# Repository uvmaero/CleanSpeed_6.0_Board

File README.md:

# AERO_2023_2024_Board* singular

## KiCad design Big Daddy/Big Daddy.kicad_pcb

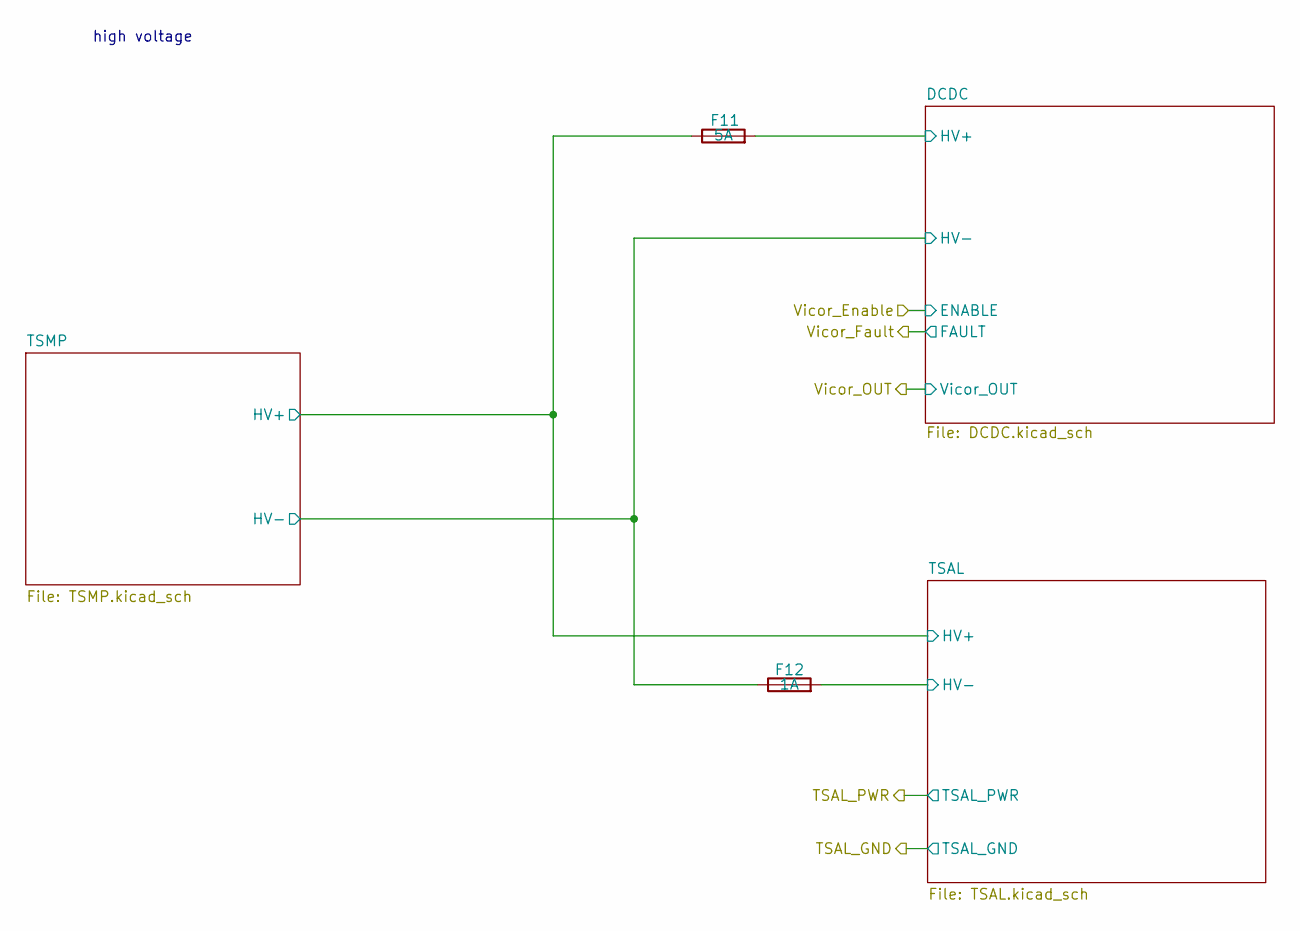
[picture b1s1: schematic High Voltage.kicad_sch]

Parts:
F11: 5A; Fuseholder_Cylinder-5x20mm_Schurter_0031_8201_Horizontal_Op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
F12: 1A; Fuseholder_Cylinder-5x20mm_Schurter_0031_8201_Horizontal_Op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

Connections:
/High Voltage/DCDC/HV+: F11.2; also elsewhere on the board
/High Voltage/DCDC/HV-: F12.1; also elsewhere on the board
/High Voltage/TSAL/HV+: F11.1; also elsewhere on the board
/High Voltage/TSAL/HV-: F12.2; also elsewhere on the board

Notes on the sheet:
high voltage

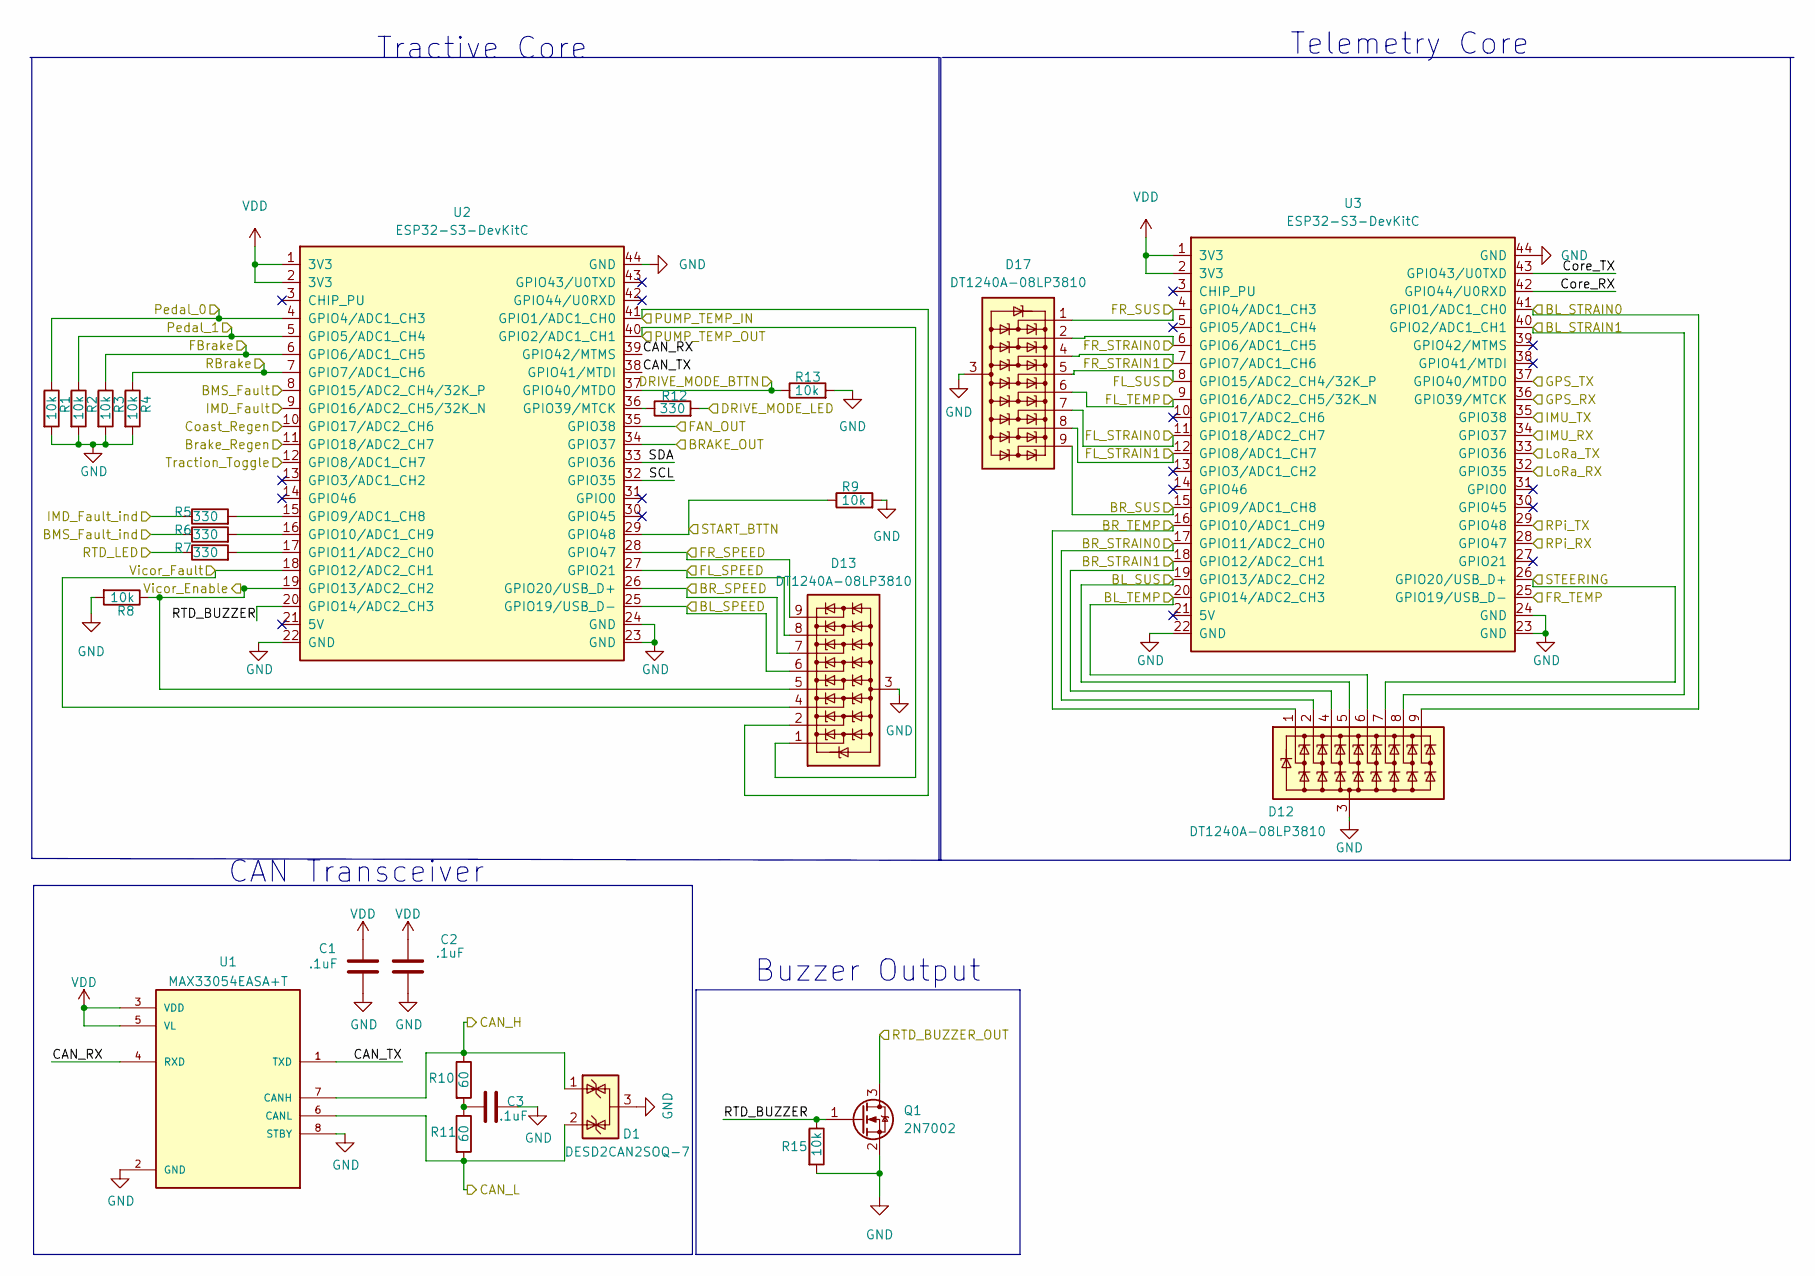
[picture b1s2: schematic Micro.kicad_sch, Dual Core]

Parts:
C1, C2, C3: .1uF; C_0603_1608Metric_Pad1.08x0.95mm_HandSolder; Manufacturer_Part_Number CC0603KRX7R7BB104; Digikey part number 311-1088-1-ND
D1: DESD2CAN2SOQ-7; SOT-23; Manufacturer_Part_Number DESD2CAN2SOQ-7; Digikey part number DESD2CAN2SOQ-7DICT-ND
D12, D13, D17: DT1240A-08LP3810; UDFN-9_1.0x3.8mm_P0.5mm; Manufacturer_Part_Number DT1240A-08LP3810-7; Digikey part number DT1240A-08LP3810-7DICT-ND
Q1: 2N7002; SOT-23; Manufacturer_Part_Number 2N7002; Digikey part number 2N7002NCT-ND
R1, R2, R3, R4, R8, R9, R13, R15: 10k; R_0603_1608Metric_Pad0.98x0.95mm_HandSolder; Manufacturer_Part_Number RK73H1JTTD1002F; Digikey part number 2019-RK73H1JTTD1002FCT-ND
R5, R6, R7, R12: 330; R_0603_1608Metric_Pad0.98x0.95mm_HandSolder; Manufacturer_Part_Number WK73R1JTTD331J; Digikey part number 2019-WK73R1JTTD331JCT-ND
R10, R11: 60; R_0603_1608Metric_Pad0.98x0.95mm_HandSolder; Manufacturer_Part_Number P0603C60R0BNT; Digikey part number 716-P0603C60R0BNTCT-ND
U1: MAX33054EASA+T; SOIC127P600X175-8N; Manufacturer_Part_Number MAX33054EASA+T; Digikey part number 175-MAX33054EASA+TCT-ND
U2, U3: ESP32-S3-DevKitC; Manufacturer_Part_Number ESP32-S3-DEVKITC-1U-N8R8; Digikey part number 1965-ESP32-S3-DEVKITC-1U-N8R8-ND

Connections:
/Connectors/BL_SPEED: D13.6 (K5), U2.25 (GPIO19/USB_D-); also elsewhere on the board
/Connectors/BL_STRAIN0: D12.9 (K8), U3.41 (GPIO1/ADC1_CH0); also elsewhere on the board
/Connectors/BL_STRAIN1: D12.8 (K7), U3.40 (GPIO2/ADC1_CH1); also elsewhere on the board
/Connectors/BL_SUS: D12.5 (K4), U3.19 (GPIO13/ADC2_CH2); also elsewhere on the board
/Connectors/BL_TEMP: D12.6 (K5), U3.20 (GPIO14/ADC2_CH3); also elsewhere on the board
/Connectors/BMS_Fault_ind: R6.1; also elsewhere on the board
/Connectors/BR_SPEED: D13.7 (K6), U2.26 (GPIO20/USB_D+); also elsewhere on the board
/Connectors/BR_STRAIN0: D12.2 (K2), U3.17 (GPIO11/ADC2_CH0); also elsewhere on the board
/Connectors/BR_STRAIN1: D12.4 (K3), U3.18 (GPIO12/ADC2_CH1); also elsewhere on the board
/Connectors/BR_SUS: D17.9 (K8), U3.15 (GPIO9/ADC1_CH8); also elsewhere on the board
/Connectors/BR_TEMP: D12.1 (K1), U3.16 (GPIO10/ADC1_CH9); also elsewhere on the board
/Connectors/Brake_Regen: U2.11 (GPIO18/ADC2_CH7); also elsewhere on the board
/Connectors/CAN_H: D1.1 (K), R10.1, U1.7 (CANH); also elsewhere on the board
/Connectors/CAN_L: D1.2 (K), R11.2, U1.6 (CANL); also elsewhere on the board
/Connectors/Coast_Regen: U2.10 (GPIO17/ADC2_CH6); also elsewhere on the board
/Connectors/DRIVE_MODE_BTTN: R13.1, U2.37 (GPIO40/MTDO); also elsewhere on the board
/Connectors/DRIVE_MODE_LED: R12.2; also elsewhere on the board
/Connectors/FBrake: R3.1, U2.6 (GPIO6/ADC1_CH5); also elsewhere on the board
/Connectors/FL_SPEED: D13.8 (K7), U2.27 (GPIO21); also elsewhere on the board
/Connectors/FL_STRAIN0: D17.7 (K6), U3.11 (GPIO18/ADC2_CH7); also elsewhere on the board
/Connectors/FL_STRAIN1: D17.8 (K7), U3.12 (GPIO8/ADC1_CH7); also elsewhere on the board
/Connectors/FL_SUS: D17.5 (K4), U3.8 (GPIO15/ADC2_CH4/32K_P); also elsewhere on the board
/Connectors/FL_TEMP: D17.6 (K5), U3.9 (GPIO16/ADC2_CH5/32K_N); also elsewhere on the board
/Connectors/FR_SPEED: D13.9 (K8), U2.28 (GPIO47); also elsewhere on the board
/Connectors/FR_STRAIN0: D17.2 (K2), U3.6 (GPIO6/ADC1_CH5); also elsewhere on the board
/Connectors/FR_STRAIN1: D17.4 (K3), U3.7 (GPIO7/ADC1_CH6); also elsewhere on the board
/Connectors/FR_SUS: D17.1 (K1), U3.4 (GPIO4/ADC1_CH3); also elsewhere on the board
/Connectors/FR_TEMP: U3.25 (GPIO19/USB_D-); also elsewhere on the board
/Connectors/GPS_RX: U3.36 (GPIO39/MTCK); also elsewhere on the board
/Connectors/GPS_TX: U3.37 (GPIO40/MTDO); also elsewhere on the board
/Connectors/IMD_Fault_ind: R5.1; also elsewhere on the board
/Connectors/IMU_RX: U3.34 (GPIO37); also elsewhere on the board
/Connectors/IMU_TX: U3.35 (GPIO38); also elsewhere on the board
/Connectors/LoRa_RX: U3.32 (GPIO35); also elsewhere on the board
/Connectors/LoRa_TX: U3.33 (GPIO36); also elsewhere on the board
/Connectors/PUMP_TEMP_IN: D13.2 (K2), U2.41 (GPIO1/ADC1_CH0); also elsewhere on the board
/Connectors/PUMP_TEMP_OUT: D13.1 (K1), U2.40 (GPIO2/ADC1_CH1); also elsewhere on the board
/Connectors/Pedal_0: R1.1, U2.4 (GPIO4/ADC1_CH3); also elsewhere on the board
/Connectors/Pedal_1: R2.1, U2.5 (GPIO5/ADC1_CH4); also elsewhere on the board
/Connectors/RBrake: R4.1, U2.7 (GPIO7/ADC1_CH6); also elsewhere on the board
/Connectors/RPi_RX: U3.28 (GPIO47); also elsewhere on the board
/Connectors/RPi_TX: U3.29 (GPIO48); also elsewhere on the board
/Connectors/RTD_BUZZER_OUT: Q1.3 (D); also elsewhere on the board
/Connectors/RTD_LED: R7.1; also elsewhere on the board
/Connectors/START_BTTN: R9.1, U2.29 (GPIO48); also elsewhere on the board
/Connectors/STEERING: D12.7 (K6), U3.26 (GPIO20/USB_D+); also elsewhere on the board
/Cooling/Brake_SIG_Out: U2.34 (GPIO37); also elsewhere on the board
/Cooling/Fan_SIG_Out: U2.35 (GPIO38); also elsewhere on the board
/High Voltage/Vicor_Enable: D13.5 (K4), R8.1, U2.19 (GPIO13/ADC2_CH2); also elsewhere on the board
/High Voltage/Vicor_Fault: D13.4 (K3), U2.18 (GPIO12/ADC2_CH1); also elsewhere on the board
/Latching/BMS_IND: U2.8 (GPIO15/ADC2_CH4/32K_P); also elsewhere on the board
/Latching/IMD_IND: U2.9 (GPIO16/ADC2_CH5/32K_N); also elsewhere on the board
/Microcontrolller/CAN_RX: U1.4 (RXD), U2.39 (GPIO42/MTMS)
/Microcontrolller/CAN_TX: U1.1 (TXD), U2.38 (GPIO41/MTDI)
/Microcontrolller/Core_RX: U3.42 (GPIO44/U0RXD)
/Microcontrolller/Core_TX: U3.43 (GPIO43/U0TXD)
/Microcontrolller/RTD_BUZZER: Q1.1 (G), R15.1, U2.20 (GPIO14/ADC2_CH3)
/Microcontrolller/SCL: U2.32 (GPIO35)
/Microcontrolller/SDA: U2.33 (GPIO36)
/Microcontrolller/Traction_Toggle: U2.12 (GPIO8/ADC1_CH7)
GND: C1.2, C2.2, C3.2, D1.3 (A), D12.3 (A), D13.3 (A), D17.3 (A), Q1.2 (S), R1.2, R2.2, R3.2, R4.2, R8.2, R9.2, R13.2, R15.2, U1.2 (GND), U1.8 (STBY), U2.22 (GND), U2.23 (GND), U2.24 (GND), U2.44 (GND), U3.22 (GND), U3.23 (GND), U3.24 (GND), U3.44 (GND); also elsewhere on the board
unnamed: C3.1, R10.2, R11.1
unnamed: R5.2, U2.15 (GPIO9/ADC1_CH8)
unnamed: R6.2, U2.16 (GPIO10/ADC1_CH9)
unnamed: R7.2, U2.17 (GPIO11/ADC2_CH0)
unnamed: R12.1, U2.36 (GPIO39/MTCK)
VDD: C1.1, C2.1, U1.3 (VDD), U1.5 (VL), U2.1 (3V3), U2.2 (3V3), U3.1 (3V3), U3.2 (3V3); also elsewhere on the board

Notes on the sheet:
CAN Transceiver
Buzzer Output
Telemetry Core
Tractive Core

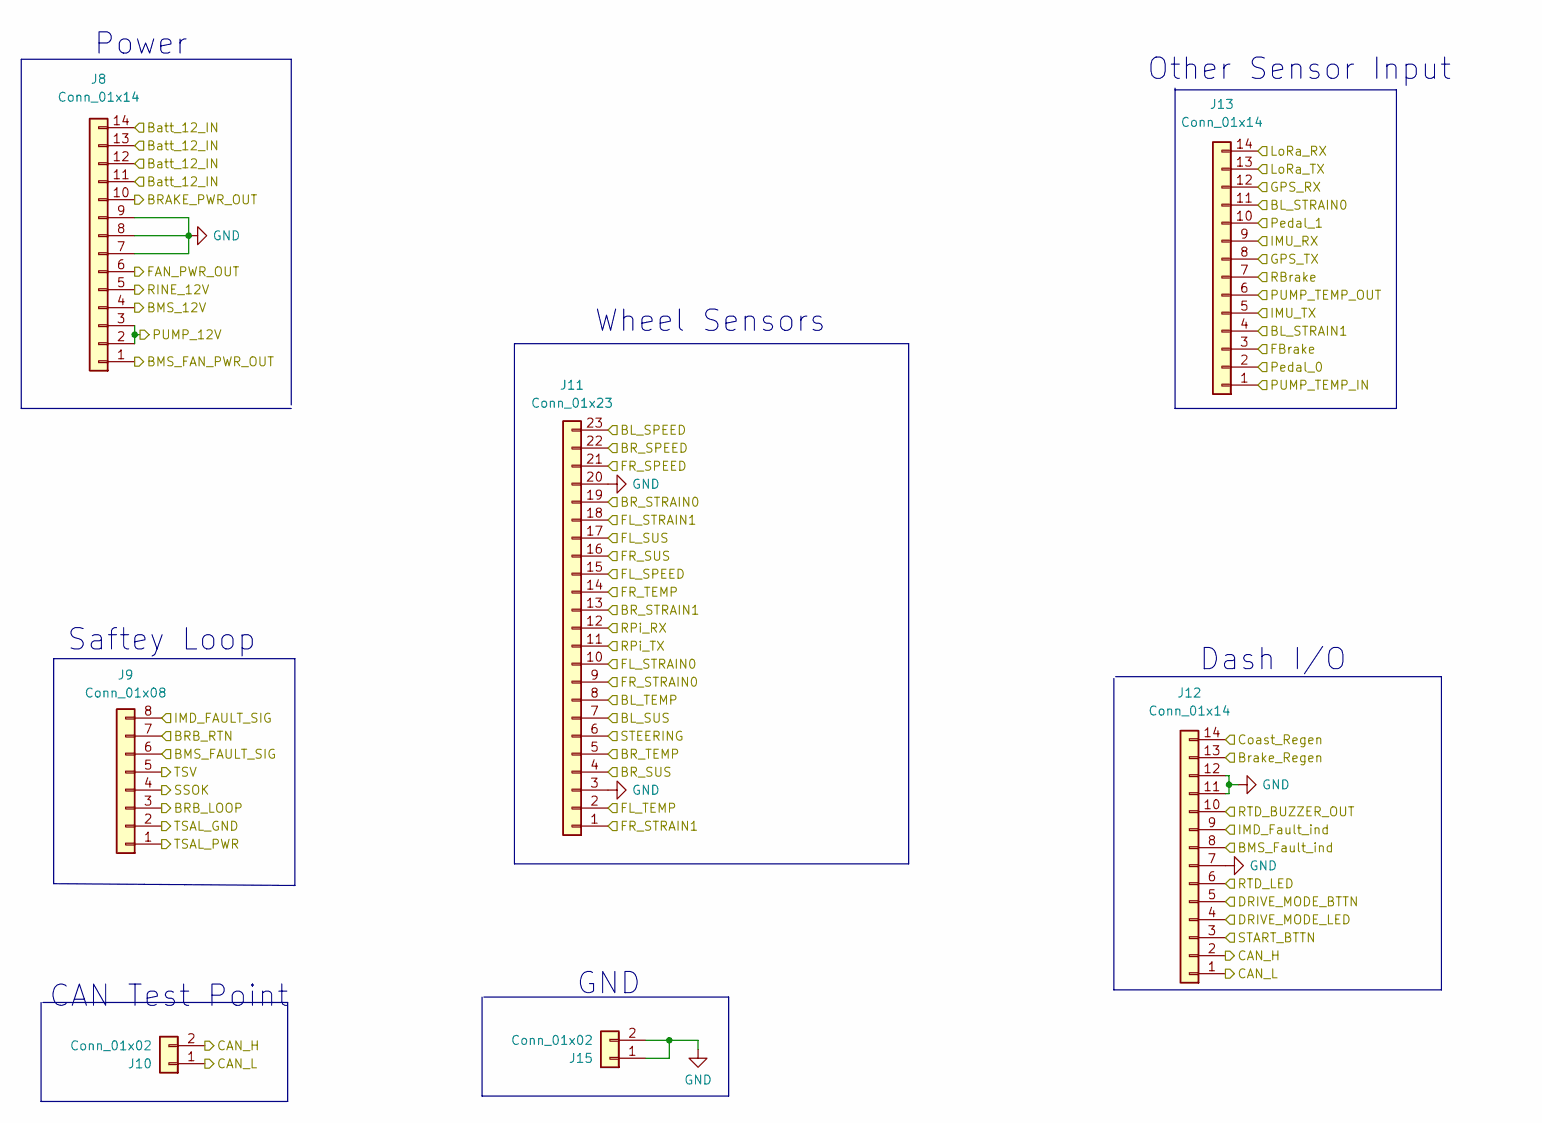
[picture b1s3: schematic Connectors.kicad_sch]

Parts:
J8, J12, J13: Conn_01x14; TE_1-776266-1_14pin_Horizontal
J9: Conn_01x08; TE_1-776280-1_8pin_Horizontal
J10, J15: Conn_01x02; TE_MATE-N-LOK_1-770866-x_1x02_P4.14mm_Vertical
J11: Conn_01x23; TE_1-770669-1_23pin_Horizontal

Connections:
/Connectors/BL_SPEED: J11.23; also elsewhere on the board
/Connectors/BL_STRAIN0: J13.11; also elsewhere on the board
/Connectors/BL_STRAIN1: J13.4; also elsewhere on the board
/Connectors/BL_SUS: J11.7; also elsewhere on the board
/Connectors/BL_TEMP: J11.8; also elsewhere on the board
/Connectors/BMS_12V: J8.4; also elsewhere on the board
/Connectors/BMS_FAN_PWR_OUT: J8.1; also elsewhere on the board
/Connectors/BMS_FAULT_SIG: J9.6; also elsewhere on the board
/Connectors/BMS_Fault_ind: J12.8; also elsewhere on the board
/Connectors/BRAKE_PWR_OUT: J8.10; also elsewhere on the board
/Connectors/BRB_LOOP: J9.3; also elsewhere on the board
/Connectors/BRB_RTN: J9.7; also elsewhere on the board
/Connectors/BR_SPEED: J11.22; also elsewhere on the board
/Connectors/BR_STRAIN0: J11.19; also elsewhere on the board
/Connectors/BR_STRAIN1: J11.13; also elsewhere on the board
/Connectors/BR_SUS: J11.4; also elsewhere on the board
/Connectors/BR_TEMP: J11.5; also elsewhere on the board
/Connectors/Batt_12_IN: J8.11, J8.12, J8.13, J8.14; also elsewhere on the board
/Connectors/Brake_Regen: J12.13; also elsewhere on the board
/Connectors/CAN_H: J10.2, J12.2; also elsewhere on the board
/Connectors/CAN_L: J10.1, J12.1; also elsewhere on the board
/Connectors/Coast_Regen: J12.14; also elsewhere on the board
/Connectors/DRIVE_MODE_BTTN: J12.5; also elsewhere on the board
/Connectors/DRIVE_MODE_LED: J12.4; also elsewhere on the board
/Connectors/FAN_PWR_OUT: J8.6; also elsewhere on the board
/Connectors/FBrake: J13.3; also elsewhere on the board
/Connectors/FL_SPEED: J11.15; also elsewhere on the board
/Connectors/FL_STRAIN0: J11.10; also elsewhere on the board
/Connectors/FL_STRAIN1: J11.18; also elsewhere on the board
/Connectors/FL_SUS: J11.17; also elsewhere on the board
/Connectors/FL_TEMP: J11.2; also elsewhere on the board
/Connectors/FR_SPEED: J11.21; also elsewhere on the board
/Connectors/FR_STRAIN0: J11.9; also elsewhere on the board
/Connectors/FR_STRAIN1: J11.1; also elsewhere on the board
/Connectors/FR_SUS: J11.16; also elsewhere on the board
/Connectors/FR_TEMP: J11.14; also elsewhere on the board
/Connectors/GPS_RX: J13.12; also elsewhere on the board
/Connectors/GPS_TX: J13.8; also elsewhere on the board
/Connectors/IMD_FAULT_SIG: J9.8; also elsewhere on the board
/Connectors/IMD_Fault_ind: J12.9; also elsewhere on the board
/Connectors/IMU_RX: J13.9; also elsewhere on the board
/Connectors/IMU_TX: J13.5; also elsewhere on the board
/Connectors/LoRa_RX: J13.14; also elsewhere on the board
/Connectors/LoRa_TX: J13.13; also elsewhere on the board
/Connectors/PUMP_12V: J8.2, J8.3; also elsewhere on the board
/Connectors/PUMP_TEMP_IN: J13.1; also elsewhere on the board
/Connectors/PUMP_TEMP_OUT: J13.6; also elsewhere on the board
/Connectors/Pedal_0: J13.2; also elsewhere on the board
/Connectors/Pedal_1: J13.10; also elsewhere on the board
/Connectors/RBrake: J13.7; also elsewhere on the board
/Connectors/RINE_12V: J8.5; also elsewhere on the board
/Connectors/RPi_RX: J11.12; also elsewhere on the board
/Connectors/RPi_TX: J11.11; also elsewhere on the board
/Connectors/RTD_BUZZER_OUT: J12.10; also elsewhere on the board
/Connectors/RTD_LED: J12.6; also elsewhere on the board
/Connectors/SSOK: J9.4, J9.5; also elsewhere on the board
/Connectors/START_BTTN: J12.3; also elsewhere on the board
/Connectors/STEERING: J11.6; also elsewhere on the board
/Connectors/TSAL_GND: J9.2; also elsewhere on the board
/Connectors/TSAL_PWR: J9.1; also elsewhere on the board
GND: J8.7, J8.8, J8.9, J11.3, J11.20, J12.7, J12.11, J12.12, J15.1, J15.2; also elsewhere on the board

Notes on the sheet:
Power
Wheel Sensors
CAN Test Point
GND
Other Sensor Input
Dash I/O
Saftey Loop

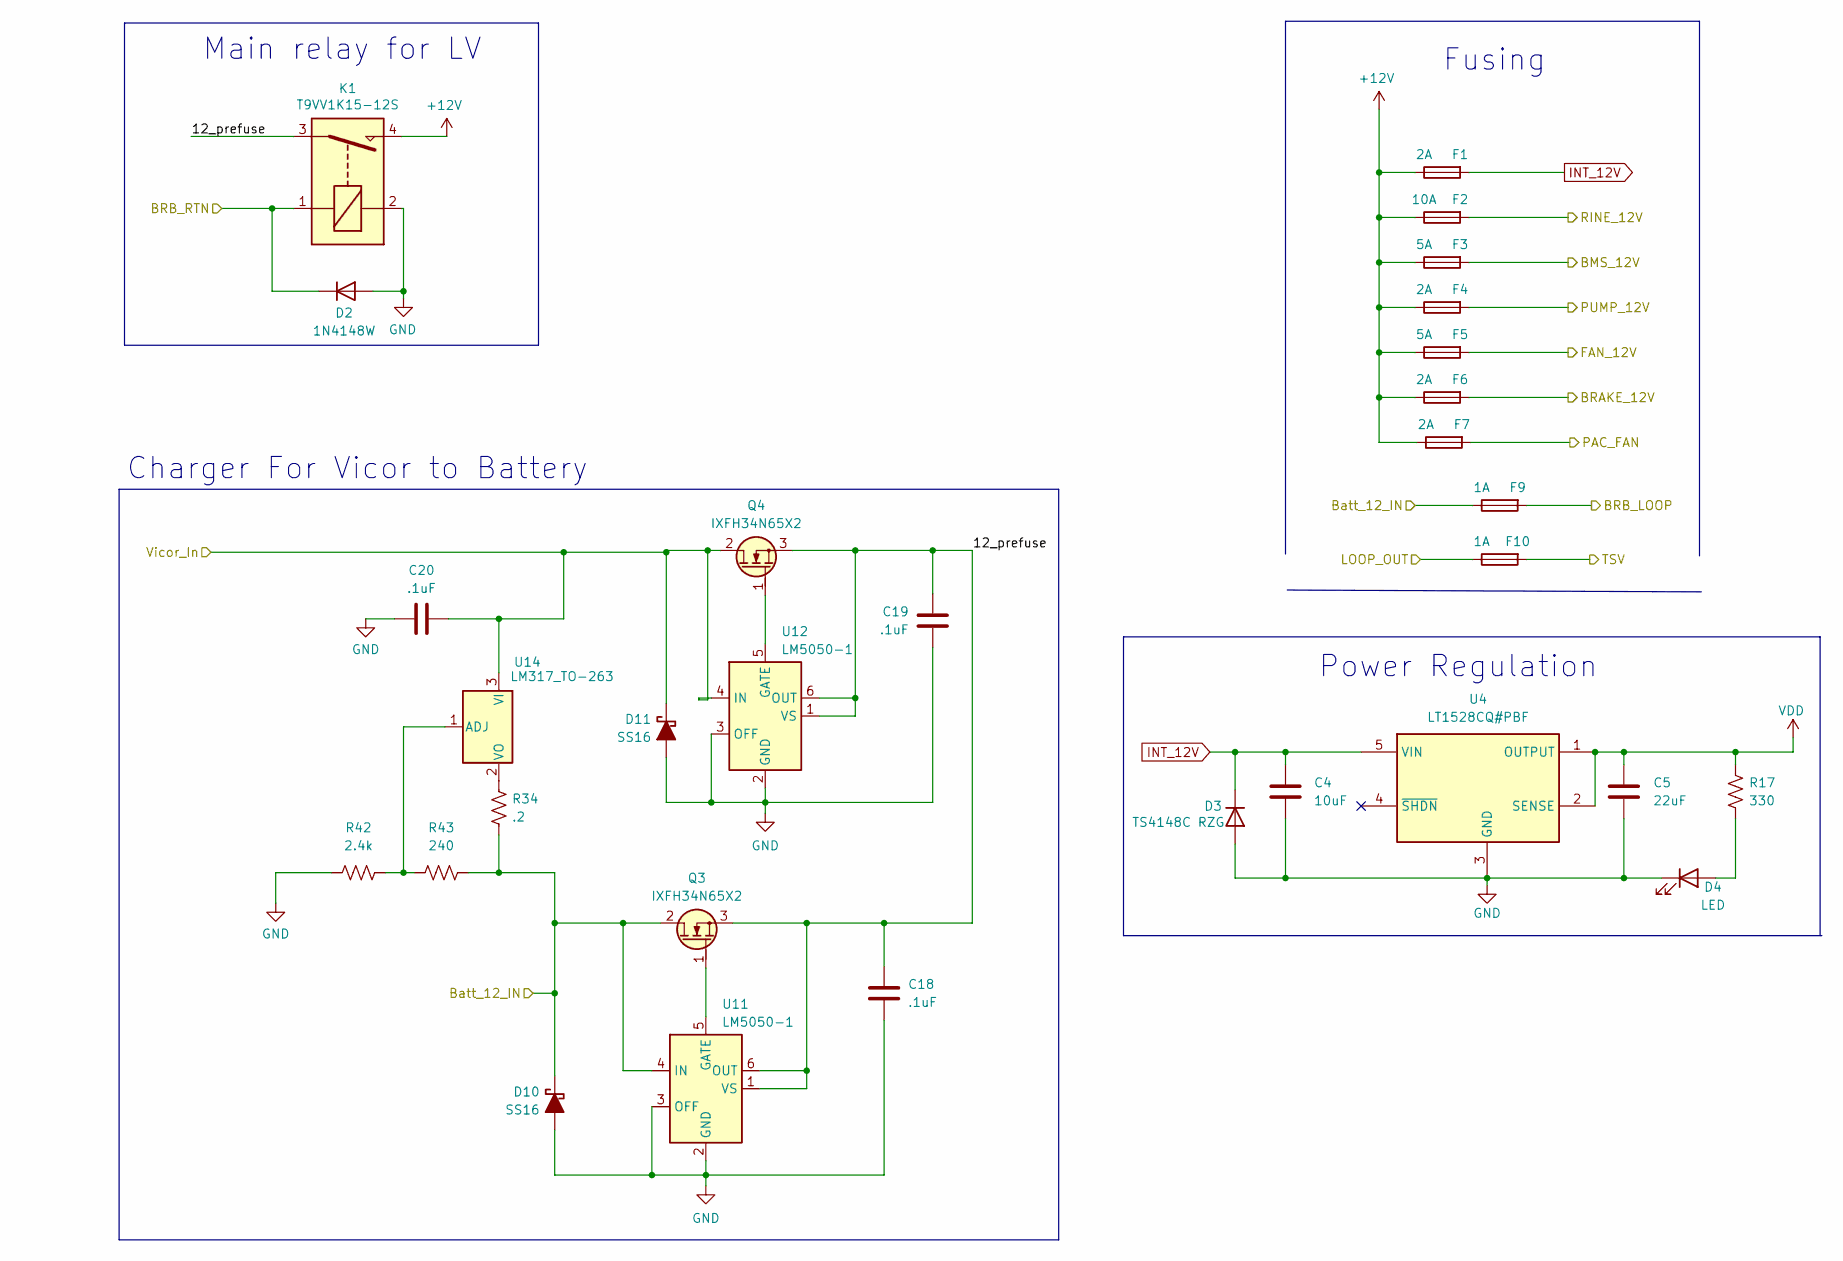
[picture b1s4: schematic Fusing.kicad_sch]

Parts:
C4: 10uF; C_0603_1608Metric_Pad1.08x0.95mm_HandSolder; Manufacturer_Part_Number CL10A106KQ8NNNC; Digikey part number 1276-1038-1-ND
C5: 22uF; C_0603_1608Metric_Pad1.08x0.95mm_HandSolder; Manufacturer_Part_Number CL10A226MP8NUNE; Digikey part number 1276-1274-1-ND
C18, C19, C20: .1uF; C_0603_1608Metric_Pad1.08x0.95mm_HandSolder; Manufacturer_Part_Number CC0603KRX7R7BB104; Digikey part number 311-1088-1-ND
D2: 1N4148W; D_SOD-123; Manufacturer_Part_Number 1N4148W; Digikey part number 1655-1N4148WCT-ND
D3: TS4148C RZG; D_0603_1608Metric_Pad1.05x0.95mm_HandSolder; Manufacturer_Part_Number TS4148 RCG; Digikey part number 1801-TS4148RCGCT-ND
D4: LED; LED_0603_1608Metric_Pad1.05x0.95mm_HandSolder
D10, D11: SS16; D_SMA; Manufacturer_Part_Number SS16T3G; Digikey part number SS16T3GOSCT-ND
F1, F4, F6, F7: 2A; Fuseholder_Blade_Mini_Keystone_3568
F2: 10A; Fuseholder_Blade_Mini_Keystone_3568
F3, F5: 5A; Fuseholder_Blade_Mini_Keystone_3568
F9, F10: 1A; Fuseholder_Blade_Mini_Keystone_3568
K1: T9VV1K15-12S; RELAY_T9VV1K15-12S; Manufacturer_Part_Number T9VV1K15-12S; Digikey part number PB2352-ND
Q3, Q4: IXFH34N65X2; TO-247-3_Vertical_GDS
R17: 330; R_0603_1608Metric_Pad0.98x0.95mm_HandSolder; Manufacturer_Part_Number WK73R1JTTD331J; Digikey part number 2019-WK73R1JTTD331JCT-ND
R34: .2; R_0805_2012Metric_Pad1.20x1.40mm_HandSolder; Manufacturer_Part_Number ERJ-6DSFR20V; Digikey part number P19315CT-ND
R42: 2.4k; R_0603_1608Metric_Pad0.98x0.95mm_HandSolder; Manufacturer_Part_Number RC0603JR-072K4L; Digikey part number 311-2.4KGRCT-ND
R43: 240; R_0603_1608Metric_Pad0.98x0.95mm_HandSolder; Manufacturer_Part_Number CRCW0603240RFKEAC; Digikey part number 541-5280-1-ND
U4: LT1528CQ#PBF; LT1528CQPBF; Mouser Part Number 584-LT1528CQ#PBF
U11, U12: LM5050-1; TSOT-23-6
U14: LM317_TO-263; TO-263-2

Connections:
+12V: F1.1, F2.1, F3.1, F4.1, F5.1, F6.1, F7.1, K1.4
/Connectors/BMS_12V: F3.2; also elsewhere on the board
/Connectors/BMS_FAN_PWR_OUT: F7.2; also elsewhere on the board
/Connectors/BRB_LOOP: F9.2; also elsewhere on the board
/Connectors/BRB_RTN: D2.1 (K), K1.1; also elsewhere on the board
/Connectors/Batt_12_IN: D10.1 (K), F9.1, Q3.2 (D), R34.1, R43.2, U11.4 (IN); also elsewhere on the board
/Connectors/PUMP_12V: F4.2; also elsewhere on the board
/Connectors/RINE_12V: F2.2; also elsewhere on the board
/Connectors/SSOK: F10.2; also elsewhere on the board
/Cooling/BRAKE_12V: F6.2; also elsewhere on the board
/Cooling/FAN_12V: F5.2; also elsewhere on the board
/Fusing/12_prefuse: C18.1, C19.1, K1.3, Q3.3 (S), Q4.3 (S), U11.1 (VS), U11.6 (OUT), U12.1 (VS), U12.6 (OUT)
/Fusing/LOOP_OUT: F10.1; also elsewhere on the board
/Fusing/Vicor_In: C20.1, D11.1 (K), Q4.2 (D), U12.4 (IN), U14.3 (VI); also elsewhere on the board
GND: C4.2, C5.2, C18.2, C19.2, C20.2, D2.2 (A), D3.2 (A), D4.1 (K), D10.2 (A), D11.2 (A), K1.2, R42.1, U4.3 (GND), U11.2 (GND), U11.3 (OFF), U12.2 (GND), U12.3 (OFF); also elsewhere on the board
INT_12V: C4.1, D3.1 (K), F1.2, U4.5 (VIN); also elsewhere on the board
unnamed: D4.2 (A), R17.2
unnamed: Q3.1 (G), U11.5 (GATE)
unnamed: Q4.1 (G), U12.5 (GATE)
unnamed: R42.2, R43.1, U14.1 (ADJ)
unnamed: R34.2, U14.2 (VO)
VDD: C5.1, R17.1, U4.1 (OUTPUT), U4.2 (SENSE); also elsewhere on the board

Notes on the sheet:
Fusing
Power Regulation
Charger For Vicor to Battery
Main relay for LV

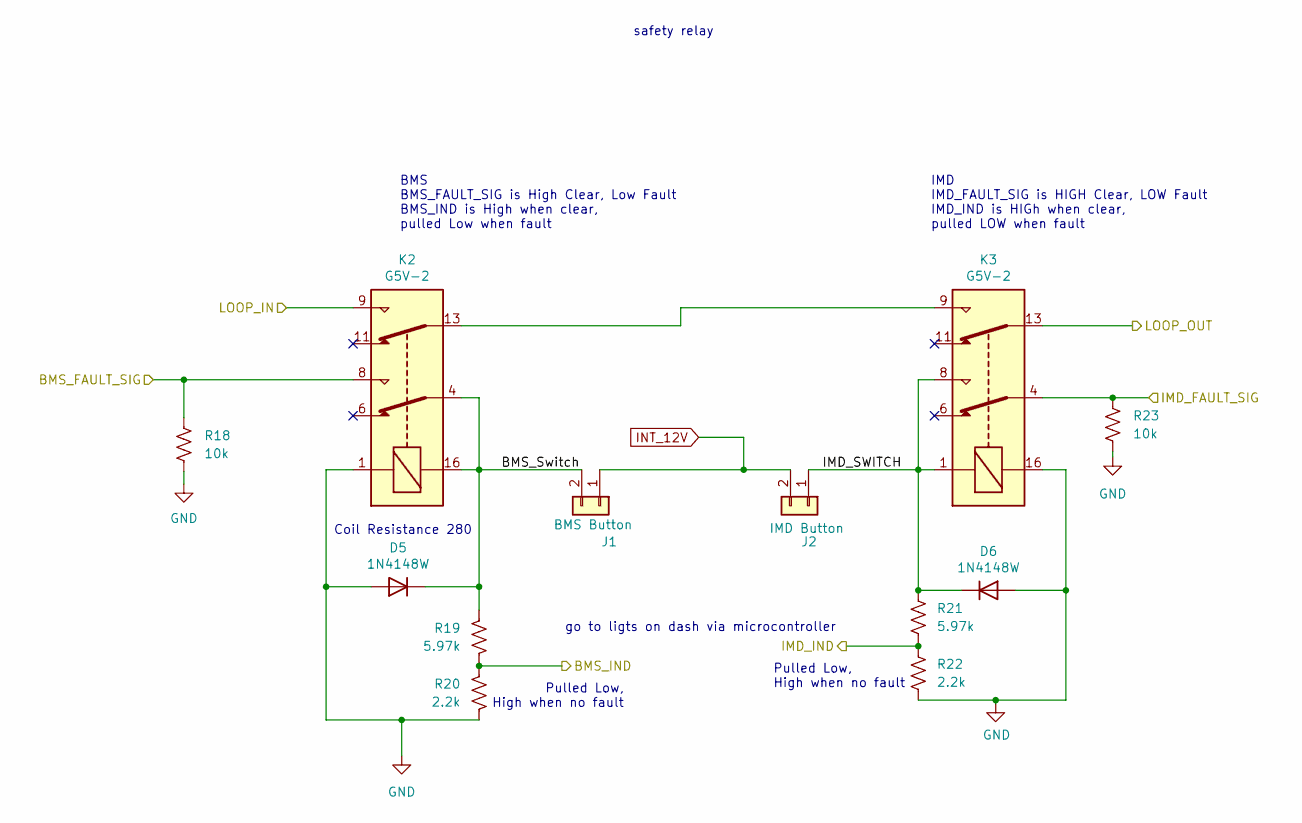
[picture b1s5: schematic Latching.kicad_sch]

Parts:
D5, D6: 1N4148W; D_SOD-123; Manufacturer_Part_Number 1N4148W; Digikey part number 1655-1N4148WCT-ND
J1: BMS Button; JST_XH_B2B-XH-AM_1x02_P2.50mm_Vertical
J2: IMD Button; JST_XH_B2B-XH-AM_1x02_P2.50mm_Vertical
K2, K3: G5V-2; Relay_DPDT_Omron_G5V-2
R18, R23: 10k; R_0603_1608Metric_Pad0.98x0.95mm_HandSolder; Manufacturer_Part_Number RK73H1JTTD1002F; Digikey part number 2019-RK73H1JTTD1002FCT-ND
R19, R21: 5.97k; R_0603_1608Metric_Pad0.98x0.95mm_HandSolder; Manufacturer_Part_Number RN73R1JTTD5971B25; Digikey part number 2019-RN73R1JTTD5971B25CT-ND
R20, R22: 2.2k; R_0603_1608Metric_Pad0.98x0.95mm_HandSolder; Manufacturer_Part_Number CRGCQ0603F2K2; Digikey part number A129692CT-ND

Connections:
/Connectors/BMS_FAULT_SIG: K2.8, R18.1; also elsewhere on the board
/Connectors/IMD_FAULT_SIG: K3.4, R23.1; also elsewhere on the board
/Fusing/LOOP_OUT: K3.13; also elsewhere on the board
/Latching/BMS_IND: R19.2, R20.1; also elsewhere on the board
/Latching/BMS_Switch: D5.1 (K), J1.2, K2.4, K2.16, R19.1
/Latching/IMD_IND: R21.2, R22.1; also elsewhere on the board
/Latching/IMD_SWITCH: D6.1 (K), J2.1, K3.1, K3.8, R21.1
GND: D5.2 (A), D6.2 (A), K2.1, K3.16, R18.2, R20.2, R22.2, R23.2; also elsewhere on the board
INT_12V: J1.1, J2.2, K2.9; also elsewhere on the board
unnamed: K2.13, K3.9

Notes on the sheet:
BMS BMS_FAULT_SIG is High Clear, Low Fault BMS_IND is High when clear, pulled Low when fault
Pulled Low, High when no fault
Coil Resistance 280
go to ligts on dash via microcontroller
safety relay
IMD IMD_FAULT_SIG is HIGH Clear, LOW Fault IMD_IND is HIGh when clear, pulled LOW when fault

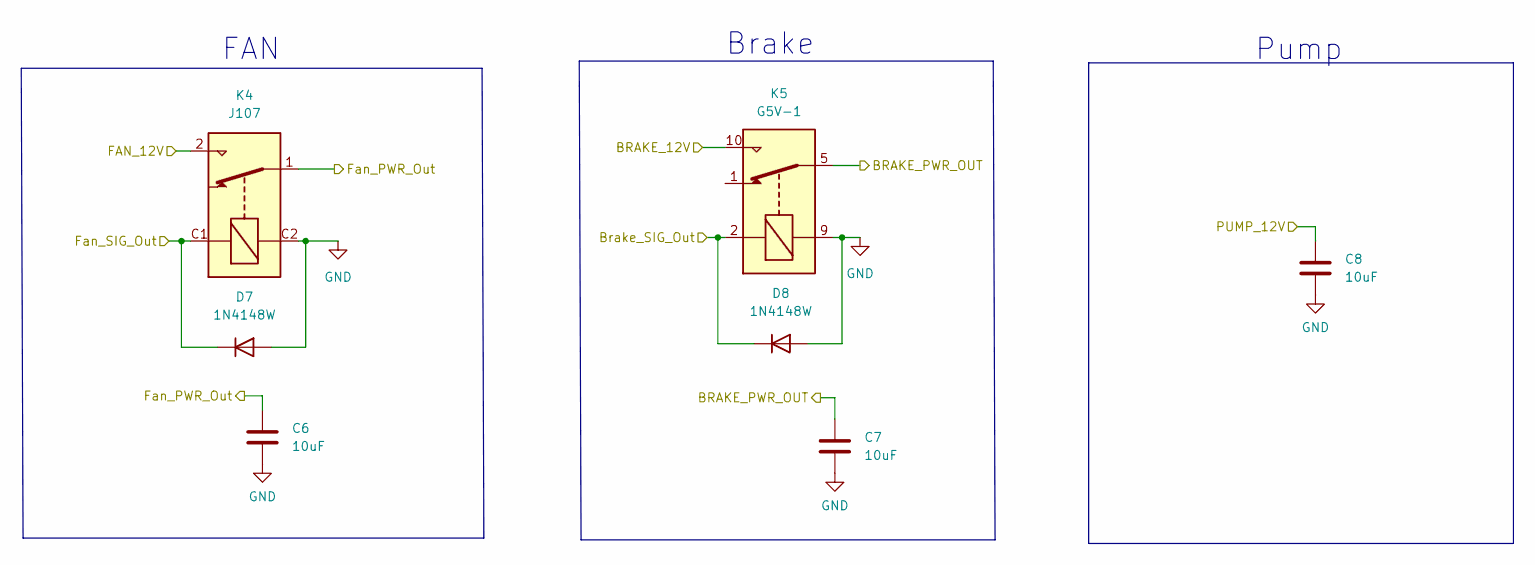
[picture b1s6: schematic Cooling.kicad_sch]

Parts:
C6, C7, C8: 10uF; C_0603_1608Metric_Pad1.08x0.95mm_HandSolder; Manufacturer_Part_Number CL10A106KQ8NNNC; Digikey part number 1276-1038-1-ND
D7, D8: 1N4148W; D_SOD-123; Manufacturer_Part_Number 1N4148W; Digikey part number 1655-1N4148WCT-ND
K4: J107; J1071AS3VDC
K5: G5V-1; Relay_SPDT_Omron_G5V-1

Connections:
/Connectors/BRAKE_PWR_OUT: C7.1, K5.5, K5.6; also elsewhere on the board
/Connectors/FAN_PWR_OUT: C6.1, K4.1; also elsewhere on the board
/Connectors/PUMP_12V: C8.1; also elsewhere on the board
/Cooling/BRAKE_12V: K5.10; also elsewhere on the board
/Cooling/Brake_SIG_Out: D8.1 (K), K5.2; also elsewhere on the board
/Cooling/FAN_12V: K4.2; also elsewhere on the board
/Cooling/Fan_SIG_Out: D7.1 (K), K4.C1; also elsewhere on the board
GND: C6.2, C7.2, C8.2, D7.2 (A), D8.2 (A), K4.C2, K5.9; also elsewhere on the board

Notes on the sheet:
Brake
FAN
Pump

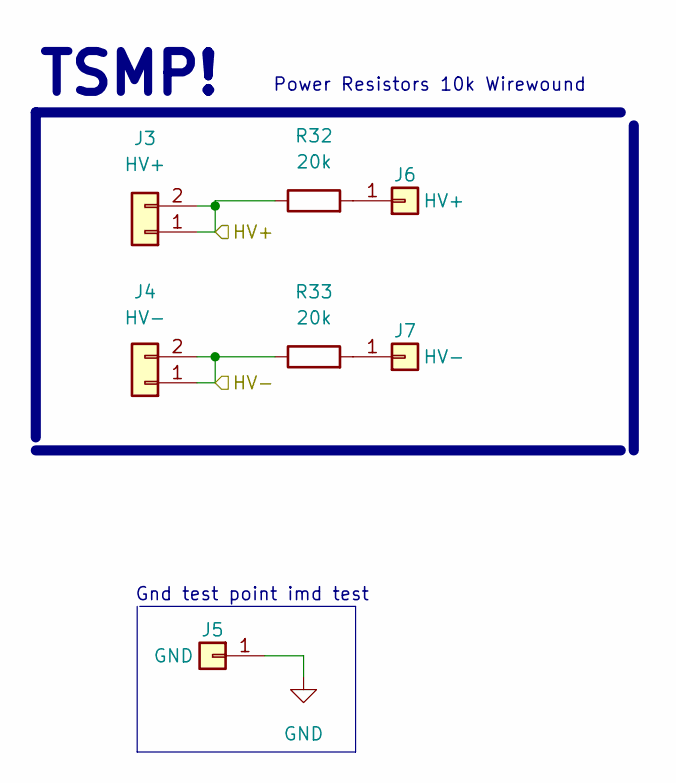
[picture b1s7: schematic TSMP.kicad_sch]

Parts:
J3: HV+; Hirose_DF63R-2P-3.96DSA_1x02_P3.96mm_Vertical
J4: HV-; Hirose_DF63R-2P-3.96DSA_1x02_P3.96mm_Vertical
J5: GND; Hirose_DF63M-1P-3.96DSA_1x01_P3.96mm_Vertical
J6: HV+; Hirose_DF63M-1P-3.96DSA_1x01_P3.96mm_Vertical
J7: HV-; Hirose_DF63M-1P-3.96DSA_1x01_P3.96mm_Vertical
R32, R33: 20k; R_Axial_DIN0309_L9.0mm_D3.2mm_P5.08mm_Vertical; Manufacturer_Part_Number CF18JT20K0; Digikey part number CF18JT20K0CT-ND

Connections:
/High Voltage/DCDC/HV-: J4.1, J4.2, R33.1; also elsewhere on the board
/High Voltage/TSAL/HV+: J3.1, J3.2, R32.1; also elsewhere on the board
GND: J5.1; also elsewhere on the board
unnamed: J6.1, R32.2
unnamed: J7.1, R33.2

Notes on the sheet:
TSMP!
Power Resistors 10k Wirewound
Gnd test point imd test
